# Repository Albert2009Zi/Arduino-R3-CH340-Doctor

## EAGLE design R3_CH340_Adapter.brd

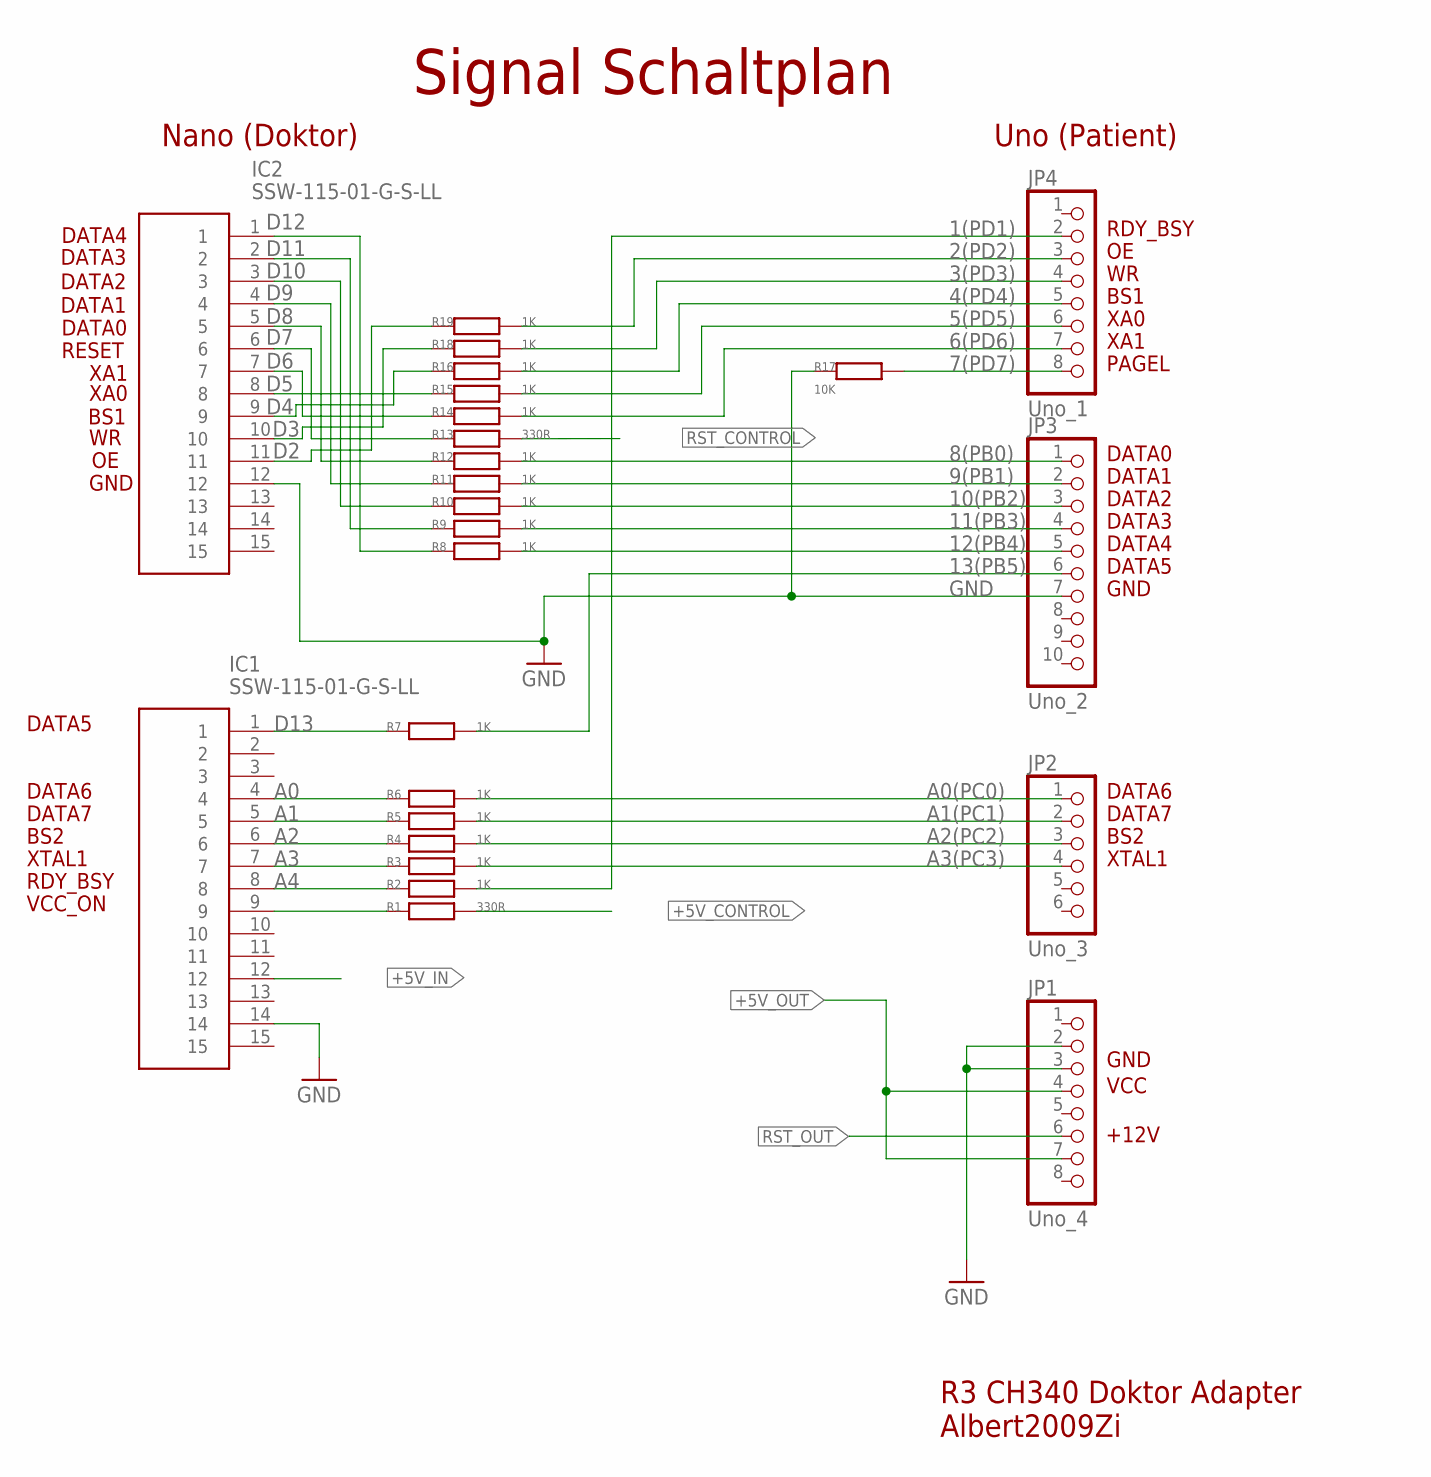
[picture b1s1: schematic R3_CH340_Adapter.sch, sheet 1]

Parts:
IC1, IC2: SSW-115-01-G-S-LL; RHDR15W79P0X254_1X15_3861X241X
JP1: Uno_4; 1X08
JP2: Uno_3; 1X06
JP3: Uno_2; 1X10
JP4: Uno_1; 1X08
R1, R13: 330R; R0805
R2, R3, R4, R5, R6, R7, R8, R9, R10, R11, R12, R14, R15, R16, R18, R19: 1K; R0805
R17: 10K; R0805

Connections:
1(PD1): JP4.2, R2.2
2(PD2): JP4.3, R19.2
3(PD3): JP4.4, R18.2
4(PD4): JP4.5, R16.2
5(PD5): JP4.6, R15.2
6(PD6): JP4.7, R14.2
7(PD7): JP4.8, R17.2
8(PB0): JP3.1, R12.2
9(PB1): JP3.2, R11.2
10(PB2): JP3.3, R10.2
11(PB3): JP3.4, R9.2
12(PB4): JP3.5, R8.2
13(PB5): JP3.6, R7.2
+5V_CONTROL: R1.2; also elsewhere on the board
+5V_IN: IC1.12; also elsewhere on the board
+5V_OUT: JP1.4, JP1.7; also elsewhere on the board
A0: IC1.4, R6.1
A0(PC0): JP2.1, R6.2
A1: IC1.5, R5.1
A1(PC1): JP2.2, R5.2
A2: IC1.6, R4.1
A2(PC2): JP2.3, R4.2
A3: IC1.7, R3.1
A3(PC3): JP2.4, R3.2
A4: IC1.8, R2.1
D2: IC2.11, R19.1
D3: IC2.10, R18.1
D4: IC2.9, R16.1
D5: IC2.8, R15.1
D6: IC2.7, R14.1
D7: IC2.6, R13.1
D8: IC2.5, R12.1
D9: IC2.4, R11.1
D10: IC2.3, R10.1
D11: IC2.2, R9.1
D12: IC2.1, R8.1
D13: IC1.1, R7.1
GND: IC1.14, IC2.12, JP1.2, JP1.3, JP3.7, R17.1; also elsewhere on the board
RST_CONTROL: R13.2; also elsewhere on the board
RST_OUT: JP1.6; also elsewhere on the board
VCC_ON: IC1.9, R1.1

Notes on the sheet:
DATA0
DATA1
DATA2
DATA3
DATA4
DATA5
PAGEL
BS1
XA0
XA1
RESET
DATA6
DATA7
BS2
XTAL1
RDY_BSY
VCC_ON
VCC
+12V
GND
Signal Schaltplan
Nano (Doktor)
Uno (Patient)
R3 CH340 Doktor Adapter Albert2009Zi

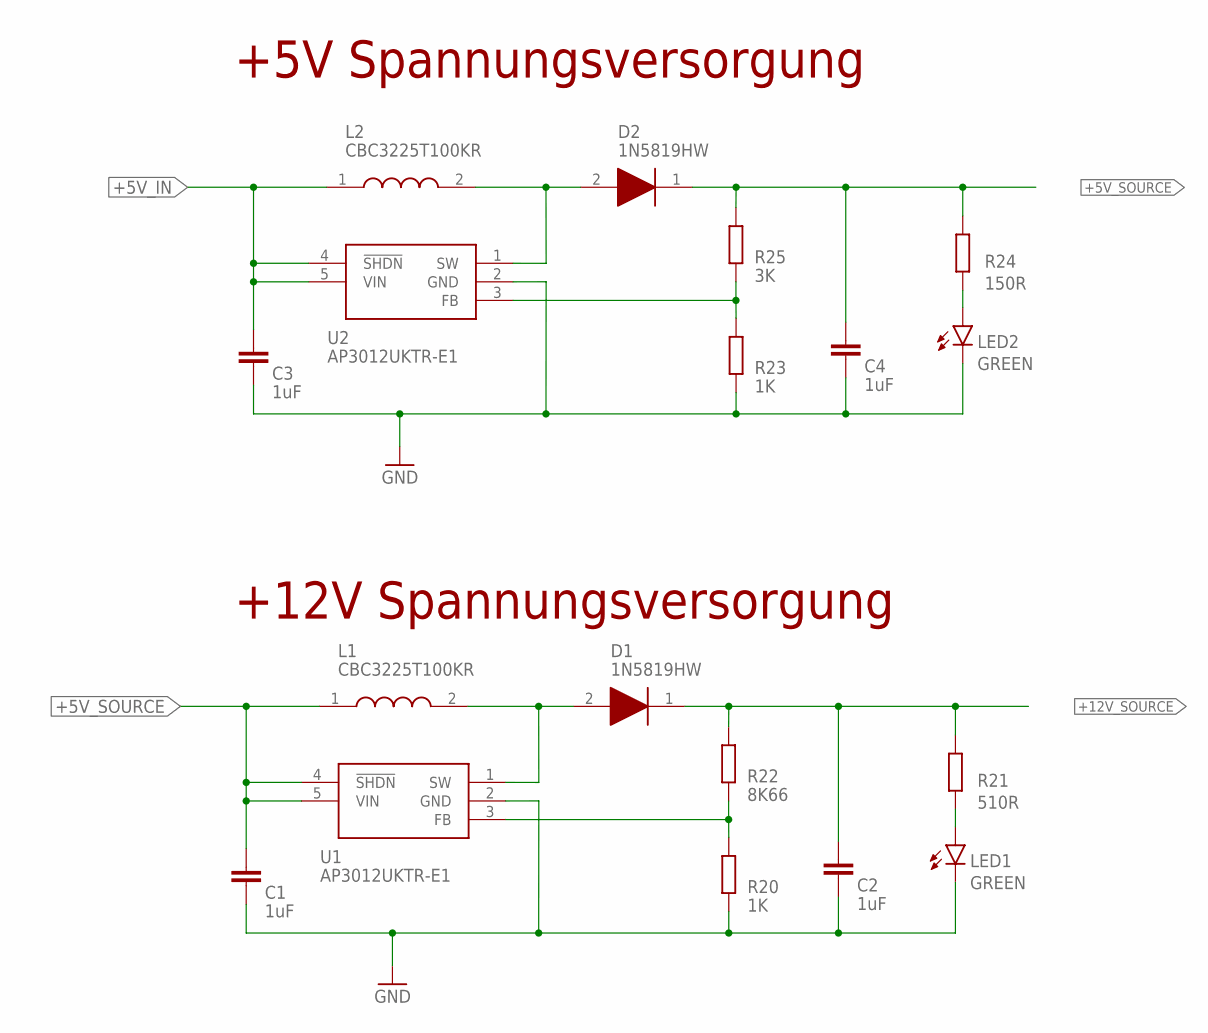
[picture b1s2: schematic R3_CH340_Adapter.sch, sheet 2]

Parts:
C1, C2, C3, C4: 1uF; C0805
D1, D2: 1N5819HW; SOD3716X145N
L1, L2: CBC3225T100KR; INDC3225X270N
LED1, LED2: GREEN; CHIP-LED0805
R20, R23: 1K; R0805
R21: 510R; R0805
R22: 8K66; R0805
R24: 150R; R0805
R25: 3K; R0805
U1, U2: AP3012UKTR-E1; SOT95P280X145-5N

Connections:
+5V_IN: C3.1, L2.1, U2.4 (!SHDN), U2.5 (VIN); also elsewhere on the board
+5V_SOURCE: C1.1, C4.1, D2.1 (K), L1.1, R24.1, R25.2, U1.4 (!SHDN), U1.5 (VIN); also elsewhere on the board
+12V_SOURCE: C2.1, D1.1 (K), R21.1, R22.2; also elsewhere on the board
GND: C1.2, C2.2, C3.2, C4.2, LED1.C, LED2.C, R20.1, R23.1, U1.2 (GND), U2.2 (GND); also elsewhere on the board
unnamed: D2.2 (A), L2.2, U2.1 (SW)
unnamed: R23.2, R25.1, U2.3 (FB)
unnamed: D1.2 (A), L1.2, U1.1 (SW)
unnamed: R20.2, R22.1, U1.3 (FB)
unnamed: LED2.A, R24.2
unnamed: LED1.A, R21.2

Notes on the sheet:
+12V Spannungsversorgung
+5V Spannungsversorgung

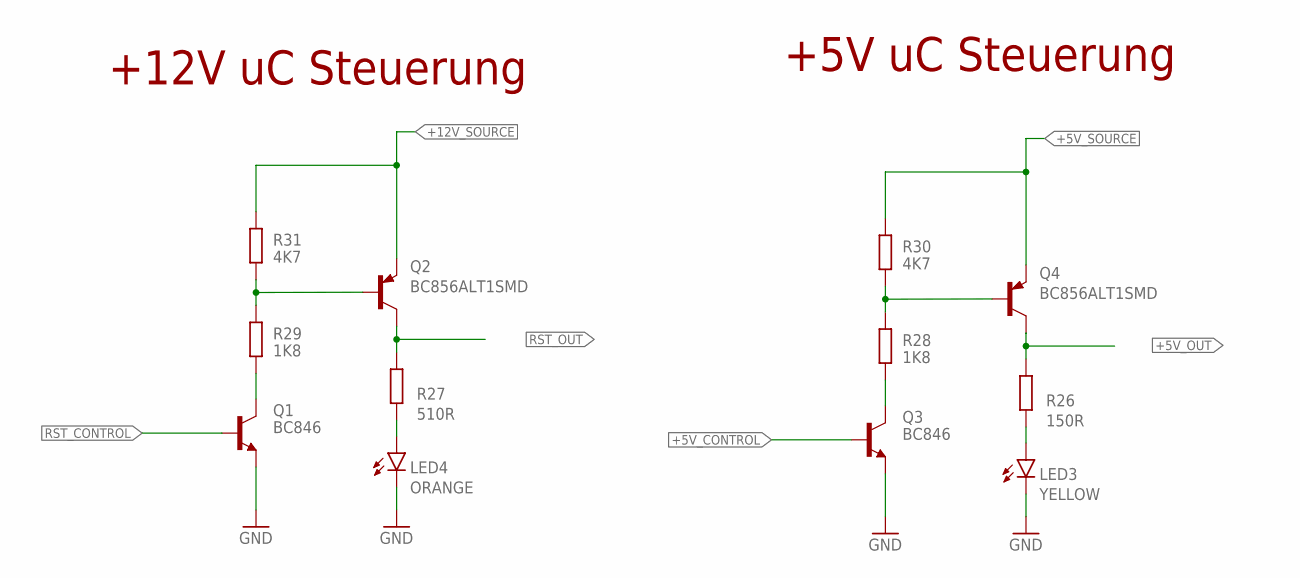
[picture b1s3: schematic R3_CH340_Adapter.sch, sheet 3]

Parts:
LED3: YELLOW; CHIP-LED0805
LED4: ORANGE; CHIP-LED0805
Q1, Q3: BC846; SOT23
Q2, Q4: BC856ALT1SMD; SOT23-BEC
R26: 150R; R0805
R27: 510R; R0805
R28, R29: 1K8; R0805
R30, R31: 4K7; R0805

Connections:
+5V_CONTROL: Q3.1 (B); also elsewhere on the board
+5V_OUT: Q4.C, R26.1; also elsewhere on the board
+5V_SOURCE: Q4.E, R30.2; also elsewhere on the board
+12V_SOURCE: Q2.E, R31.2; also elsewhere on the board
GND: LED3.C, LED4.C, Q1.2 (E), Q3.2 (E); also elsewhere on the board
unnamed: Q2.B, R29.2, R31.1
unnamed: LED4.A, R27.2
unnamed: Q4.B, R28.2, R30.1
unnamed: LED3.A, R26.2
unnamed: Q3.3 (C), R28.1
unnamed: Q1.3 (C), R29.1
RST_CONTROL: Q1.1 (B); also elsewhere on the board
RST_OUT: Q2.C, R27.1; also elsewhere on the board

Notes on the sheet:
+12V uC Steuerung
+5V uC Steuerung

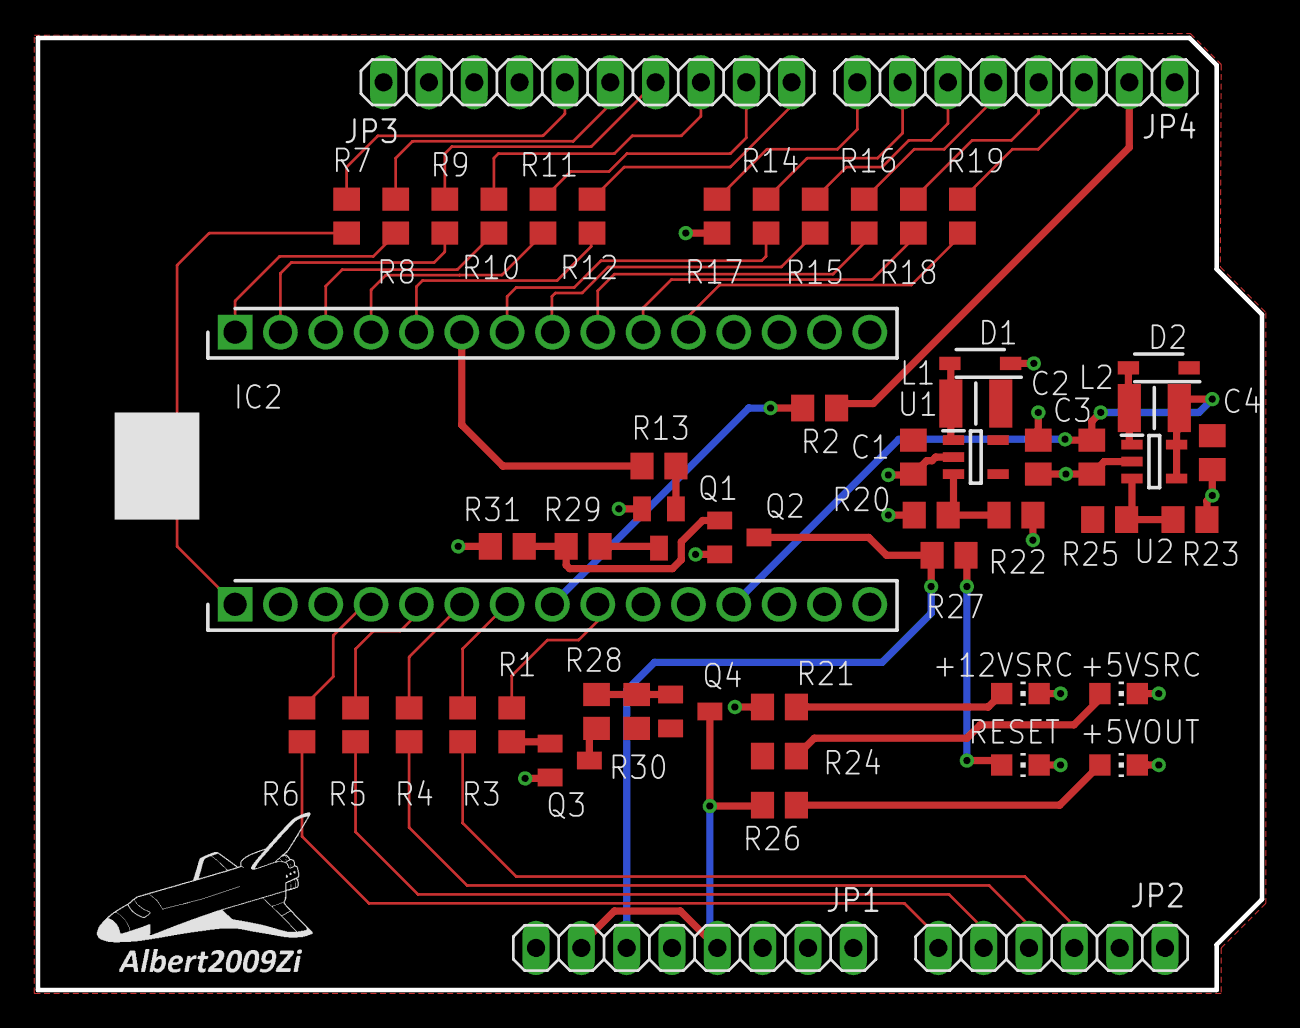
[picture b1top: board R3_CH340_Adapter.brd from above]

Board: 4 copper layers, 68.6 x 53.3 mm, 56 parts (0 on the bottom side), 55 nets.

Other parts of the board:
E$1: LOGO_SMALL

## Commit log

2023-02-19 Release v0.3 status 19022023
2023-02-19 release v0.3 final design
2023-02-28 v0.3 test OK
2023-03-14 v0.3
